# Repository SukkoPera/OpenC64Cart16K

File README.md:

# OpenC64Cart16K
OpenC64Cart16K is an Open Hardware Cartridge for the Commodore 64. It only supports 16 KB ROMs and uses a single (E)EPROM chip. It is the 16 KB counterpart to [OpenC64Cart](https://github.com/SukkoPera/OpenC64Cart).

### Summary
OpenC64Cart16K is designed to accept a 64 KB (512 Kilobit) (E)EPROM with a 27512-style pinout:

Such chips can hold up to 4 cartridge images, which can be selected by jumpers.

The recommended part is Winbond W27C512 (or W27E512, I don't understand what differences they have), which is widely available, cheap and electrically erasable, which avoids the need for a clunky UV-eraser. This is the only part that was thoroughly tested. Other parts, even smaller in size, will probably work, but will require an ad-hoc configuration.

Usage is straightforward: just insert the EEPROM in the socket making sure that the notch and all pins are aligned, set the jumpers as desired and plug the cartridge in your C64.

### Configuration
**IMPORTANT: ALWAYS TURN YOUR C64 OFF BEFORE MOVING THE CONFIGURATION JUMPERS.**

When flashing the contents, make sure that every file is exactly 16384 bytes long and just concatenate them. If your 16 KB ROM is split into two 8 KB files, concatenate them as well, with the "low" ROM before the "high" ROM.

Then use the following table to set the jumper configuration for your image of choice:

| ROM Image # | A14 | A15 |
|-------------|-----|-----|
| 1           |  L  |  L  |
| 2           |  H  |  L  |
| 3           |  L  |  H  |
| 4           |  H  |  H  |

### License
OpenC64Cart16K is Open Hardware. If you make any modifications to the board, please contribute them back.

### Support the Project
Since the project is open you are free to get the PCBs made by your preferred manufacturer, however in case you want to support the development, you can order them from PCBWay through this link:

You get my gratitude and cheap, professionally-made and good quality PCBs, I get some credit that will help with this and [other projects](https://www.pcbway.com/project/member/shareproject/?bmbid=41100). You won't even have to worry about the various PCB options, it's all pre-configured for you!

Also, if you still have to register to that site, [you can use this link](https://www.pcbway.com/setinvite.aspx?inviteid=41100) to get some bonus initial credit (and yield me some more).

Again, if you want to use another manufacturer, feel free to, don't feel obligated :). But then you can buy me a coffee if you want:

### Get Help
If you need help or have questions, you can join [the official Telegram group](https://t.me/joinchat/HUHdWBC9J9JnYIrvTYfZmg).

### Thanks
The following links were useful during the development of this project:
- https://www.c64-wiki.com/wiki/Expansion_Port
- http://blog.worldofjani.com/?p=879
- https://ist.uwaterloo.ca/~schepers/roms.html
- http://smisioto.no-ip.org/elettronica/kicad/kicad.htm

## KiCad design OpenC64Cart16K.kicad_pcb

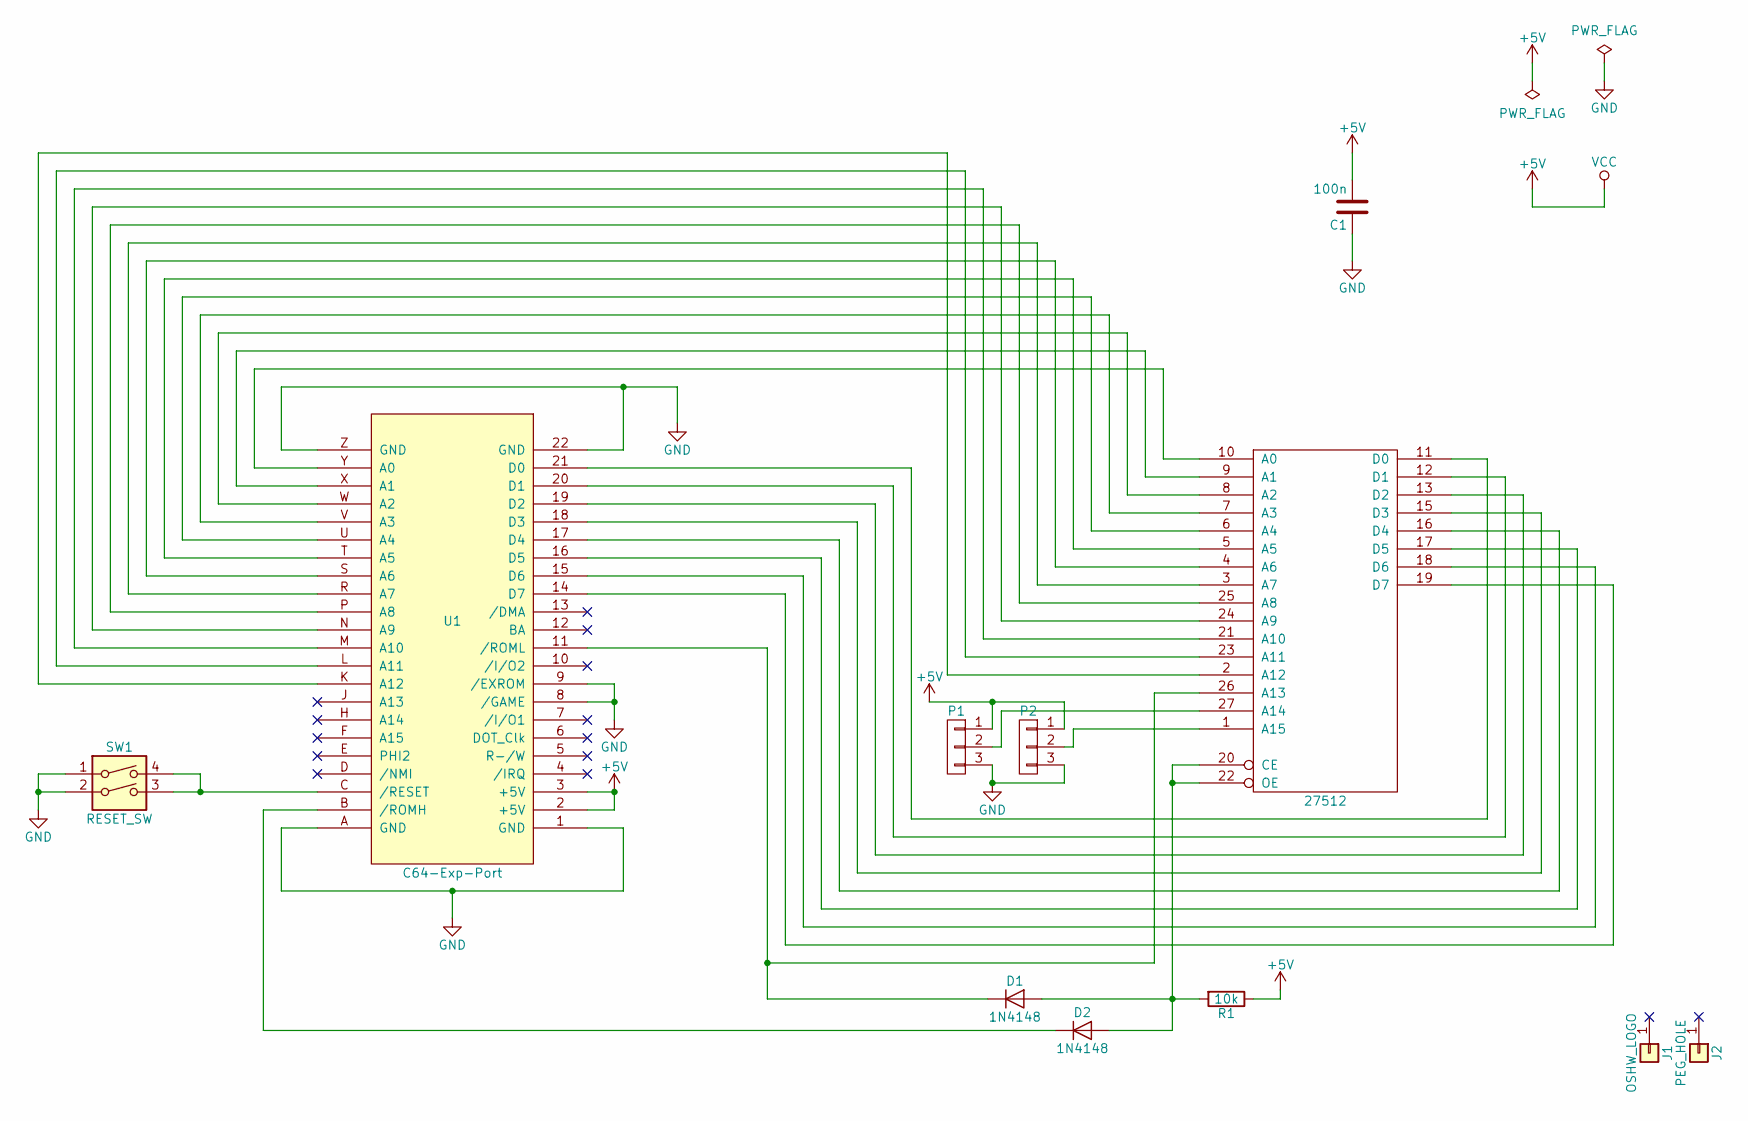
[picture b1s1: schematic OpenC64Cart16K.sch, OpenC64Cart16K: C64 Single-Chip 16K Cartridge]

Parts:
C1: 100n; C_0805+THT
D1, D2: 1N4148; D_DO35+SMA
J1: OSHW_LOGO; Logo_copper_OSHW_6x6mm
J2: PEG_HOLE; 1pin
P1, P2: CONN_01X03; Pin_Header_Straight_1x03-NoSilkS
R1: 10k; R_0805+THT-7.62mm
SW1: RESET_SW; PCB_PUSH
U1: C64-Exp-Port; C64-Cart
U2: 27512; dil_28-600_socket

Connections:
+5V: C1.2, P1.1, P2.1, R1.1, U1.2 (+5V), U1.3 (+5V), U2.28 (VCC)
GND: C1.1, P1.3, P2.3, SW1.1, SW1.2, U1.1 (GND), U1.8 (/GAME), U1.9 (/EXROM), U1.22 (GND), U1.A (GND), U1.Z (GND), U2.14 (GND)
unnamed: D1.1 (K), U1.11 (/ROML), U2.26 (A13)
unnamed: D1.2 (A), D2.2 (A), R1.2, U2.20 (CE), U2.22 (OE)
unnamed: D2.1 (K), U1.B (/ROMH)
unnamed: P1.2, U2.27 (A14)
unnamed: P2.2, U2.1 (A15)
unnamed: SW1.3, SW1.4, U1.C (/RESET)
unnamed: U1.14 (D7), U2.19 (D7)
unnamed: U1.15 (D6), U2.18 (D6)
unnamed: U1.16 (D5), U2.17 (D5)
unnamed: U1.17 (D4), U2.16 (D4)
unnamed: U1.18 (D3), U2.15 (D3)
unnamed: U1.19 (D2), U2.13 (D2)
unnamed: U1.20 (D1), U2.12 (D1)
unnamed: U1.21 (D0), U2.11 (D0)
unnamed: U1.K (A12), U2.2 (A12)
unnamed: U1.L (A11), U2.23 (A11)
unnamed: U1.M (A10), U2.21 (A10)
unnamed: U1.N (A9), U2.24 (A9)
unnamed: U1.P (A8), U2.25 (A8)
unnamed: U1.R (A7), U2.3 (A7)
unnamed: U1.S (A6), U2.4 (A6)
unnamed: U1.T (A5), U2.5 (A5)
unnamed: U1.U (A4), U2.6 (A4)
unnamed: U1.V (A3), U2.7 (A3)
unnamed: U1.W (A2), U2.8 (A2)
unnamed: U1.X (A1), U2.9 (A1)
unnamed: U1.Y (A0), U2.10 (A0)

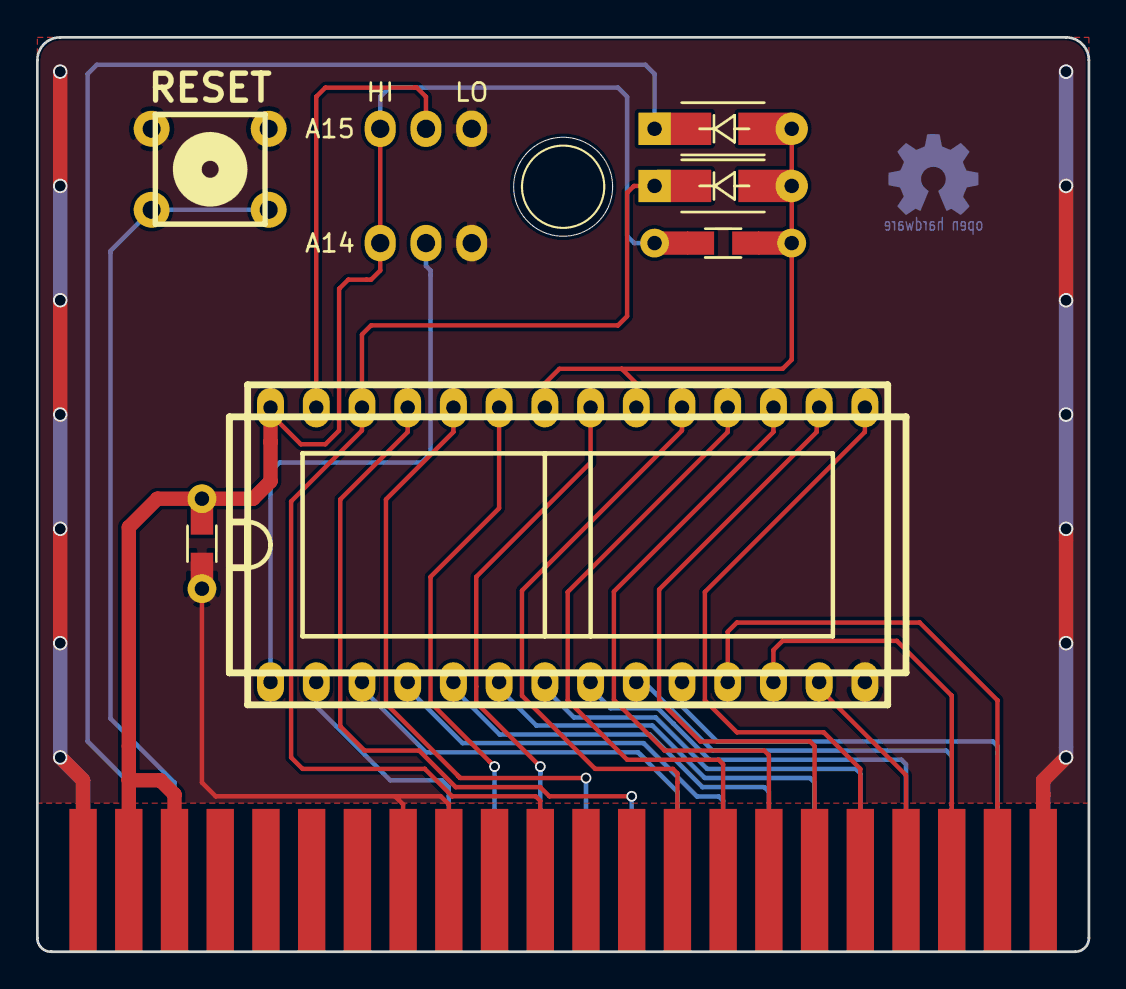
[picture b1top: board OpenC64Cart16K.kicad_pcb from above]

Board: 2 copper layers, 58.4 x 50.8 mm, 11 parts (1 on the bottom side), 29 nets.

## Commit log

2018-01-07 Final touches for V1
2018-01-07 Add schematic
2018-01-07 Add some information to README
2018-01-07 Fix typo
2018-01-07 Fix cap value
2018-02-20 Use THT/SMD combo pads for all components
2019-11-11 Minor fixes
